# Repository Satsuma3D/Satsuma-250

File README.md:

# Satsuma 250

This project is incomplete. I might pick it up one day, or you are welcome to yourselves.

GPLv3 Licensed.

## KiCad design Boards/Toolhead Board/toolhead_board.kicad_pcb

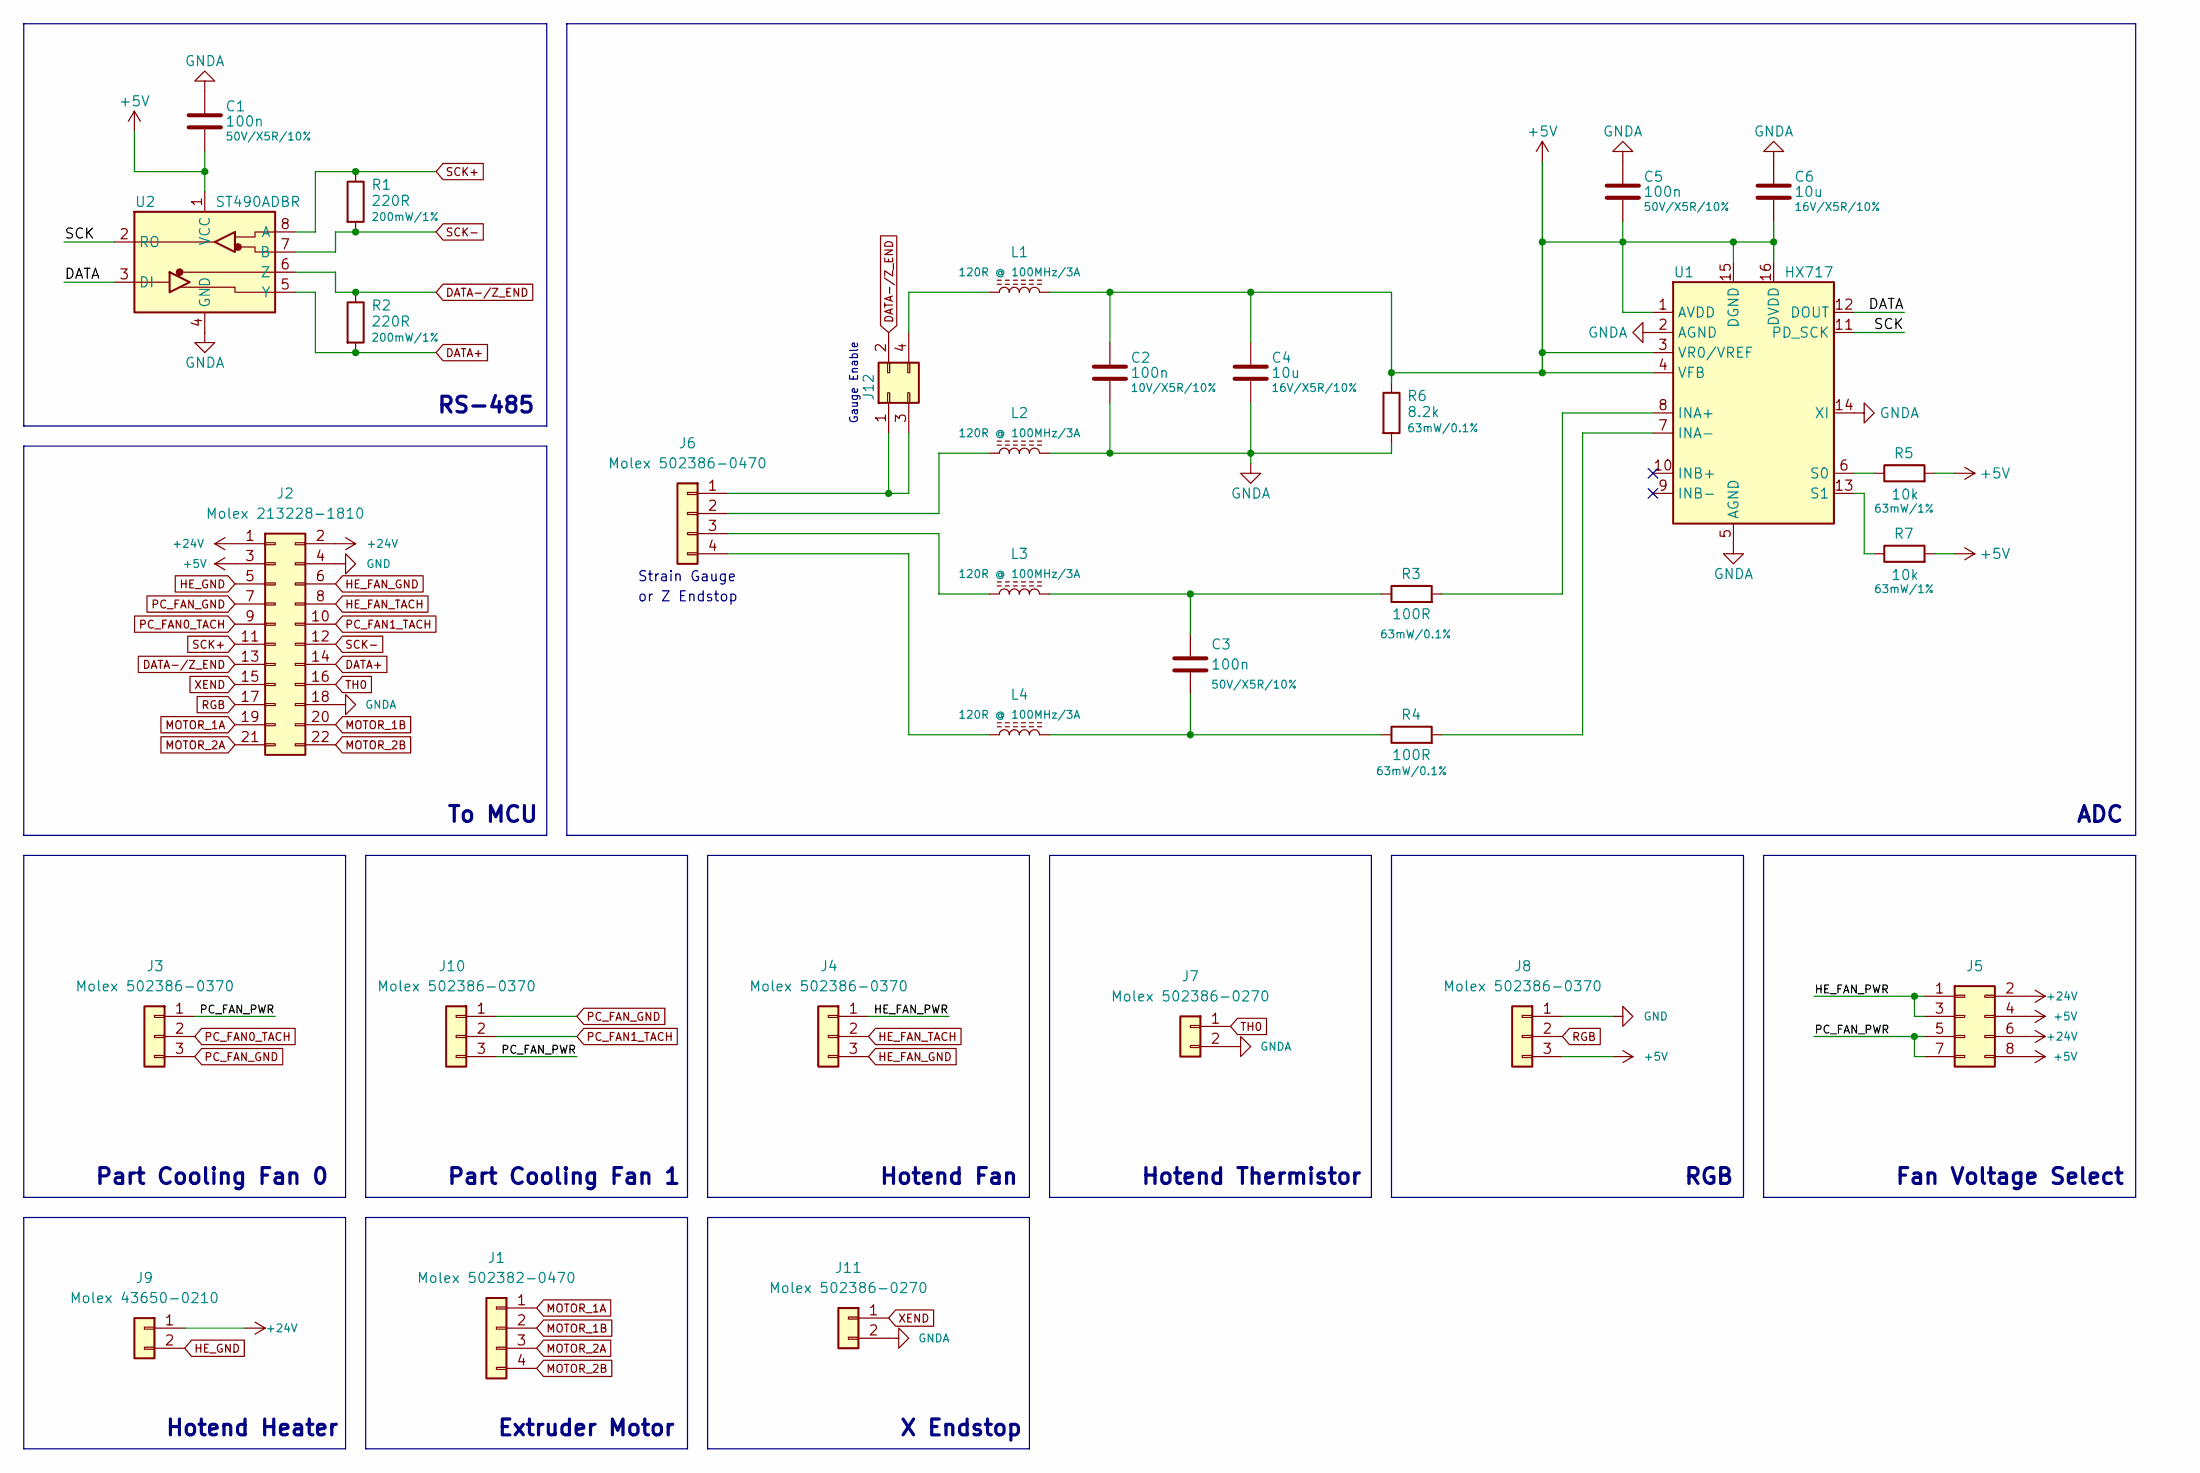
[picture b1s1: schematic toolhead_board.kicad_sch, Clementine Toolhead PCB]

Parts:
C1: 100n; C_0603_1608Metric
C2, C3, C5: 100n; C_0201_0603Metric
C4, C6: 10u; C_1206_3216Metric
J1: Molex 502382-0470; Molex_CLIK-Mate_502382-0470_1x04-1MP_P1.25mm_Vertical
J2: Molex 213228-1810; Molex_CLIK-Mate_213228-2210_1MP_P1.50mm_Horizontal
J3, J4, J8, J10: Molex 502386-0370; Molex_CLIK-Mate_502386-0370_1x03-1MP_P1.25mm_Horizontal
J5: Conn_02x04_Odd_Even; PinHeader_2x04_P2.00mm_Vertical
J6: Molex 502386-0470; Molex_CLIK-Mate_502386-0470_1x04-1MP_P1.25mm_Horizontal
J7, J11: Molex 502386-0270; Molex_CLIK-Mate_502386-0270_1x02-1MP_P1.25mm_Horizontal
J9: Molex 43650-0210; Molex_Micro-Fit_3.0_43650-0210_1x02-1MP_P3.00mm_Horizontal
J12: Conn_02x02_Odd_Even; PinHeader_2x02_P2.00mm_Vertical
L1, L2, L3, L4: 120R @ 100MHz/3A; R_0805_2012Metric
R1, R2: 220R; R_0603_1608Metric
R3, R4: 100R; R_1206_3216Metric
R5, R7: 10k; R_1206_3216Metric
R6: 8.2k; R_0201_0603Metric
U1: HX717; SOIC-16_3.9x9.9mm_P1.27mm
U2: ST490ADBR; SO-8_3.9x4.9mm_P1.27mm

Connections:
+5V: C1.2, C2.1, C4.1, C5.2, C6.2, J2.3, J5.4, J5.8, J8.3, L1.2, R5.2, R6.1, R7.2, U1.1 (AVDD), U1.3 (VR0/VREF), U1.4 (VFB), U1.15 (DGND), U1.16 (DVDD), U2.1 (VCC)
+24V: J2.1, J2.2, J5.2, J5.6, J9.1
/DATA: U1.12 (DOUT), U2.3 (DI)
/HE_FAN_PWR: J4.1, J5.1, J5.3
/PC_FAN_PWR: J3.1, J5.5, J5.7, J10.3
/SCK: U1.11 (PD_SCK), U2.2 (RO)
DATA+: J2.14, R2.2, U2.5 (Y)
DATA-/Z_END: J2.13, J12.2, R2.1, U2.6 (Z)
GND: J2.4, J8.1
GNDA: C1.1, C2.2, C4.2, C5.1, C6.1, J2.18, J7.2, J11.2, L2.2, R6.2, U1.2 (AGND), U1.5 (AGND), U1.14 (XI), U2.4 (GND)
HE_FAN_GND: J2.6, J4.3
HE_FAN_TACH: J2.8, J4.2
HE_GND: J2.5, J9.2
MOTOR_1A: J1.1, J2.19
MOTOR_1B: J1.2, J2.20
MOTOR_2A: J1.3, J2.21
MOTOR_2B: J1.4, J2.22
unnamed: C3.1, L3.2, R3.1
unnamed: C3.2, L4.2, R4.1
unnamed: J6.2, L2.1
unnamed: J6.3, L3.1
unnamed: J6.4, L4.1
unnamed: J6.1, J12.1, J12.3
unnamed: J12.4, L1.1
unnamed: R3.2, U1.8 (INA+)
unnamed: R4.2, U1.7 (INA-)
unnamed: R5.1, U1.6 (S0)
unnamed: R7.1, U1.13 (S1)
PC_FAN0_TACH: J2.9, J3.2
PC_FAN1_TACH: J2.10, J10.2
PC_FAN_GND: J2.7, J3.3, J10.1
RGB: J2.17, J8.2
SCK+: J2.11, R1.1, U2.8 (A)
SCK-: J2.12, R1.2, U2.7 (B)
TH0: J2.16, J7.1
XEND: J2.15, J11.1

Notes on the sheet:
Strain Gauge
Part Cooling Fan 0
X Endstop
Hotend Thermistor
or Z Endstop
Hotend Heater
Fan Voltage Select
RS-485
Hotend Fan
To MCU
Gauge Enable
RGB
Extruder Motor
ADC
Part Cooling Fan 1

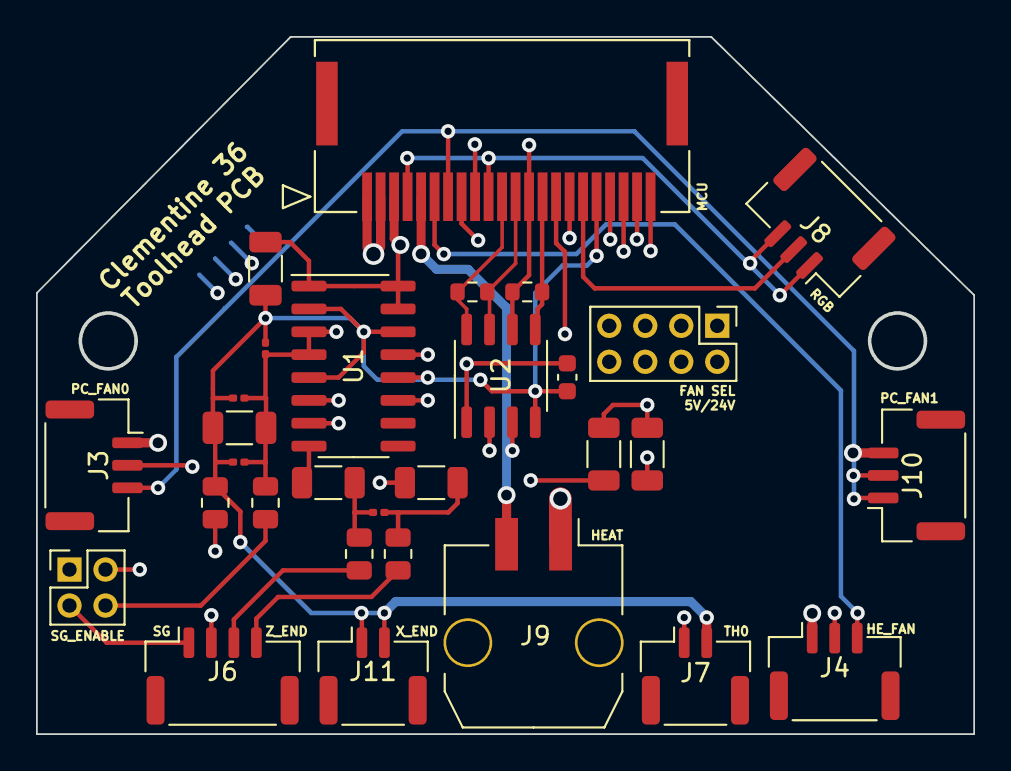
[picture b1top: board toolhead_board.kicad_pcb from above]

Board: 4 copper layers, 52.0 x 38.6 mm, 31 parts (1 on the bottom side), 36 nets.

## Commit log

2024-03-17 Update CAD
2024-03-18 Single Y extrusions
2024-03-29 CT36 Toolhead PCB
2024-03-29 Add README.md to CT36
2024-03-29 4 layer board
2024-03-29 Update image
2024-03-29 Belt paths
2024-03-30 New A/B motor assemblies
2024-03-30 Bridge cutting A/B mounts, Git LFS
2024-03-30 Add blind joints to frame
2024-03-30 Front frame blind joints are different; add gantry fasteners
2024-03-30 Fix side panel sizing
2024-03-30 Y endstop pod
2024-03-30 Cleanup the look of that ugly door
2024-03-30 Nicer side panels
2024-03-31 XY Joints
2024-04-01 Front idlers - cheers, Clee
2024-04-01 Updated render
2024-04-01 Electronics re-jig, cleaner XY joint tops
2024-04-01 Use filtered mains inlets
2024-04-01 Begun filtered mains IEC
2024-04-03 Frame updates
2024-04-03 Remove Git LFS
2024-04-23 Satsuma 250 from here on
2024-04-23 Toolhead layout
2024-05-07 Bed mounting refinements
2024-05-08 Top Z mount
2024-05-11 Z rod joints complete
2024-05-12 Gantry update
2024-05-15 A Belt
2024-05-16 Begin manual
2024-05-17 Refined motor mounts and top rod mounts
2024-05-17 Trident Z leadscrew support
2024-05-20 Pre-manual
2024-05-20 Add warning triangle
2024-05-20 Begin frame
2024-05-22 Frame preparation
2024-05-22 Grammar fix
2024-05-22 Blind joint preparation
2024-05-23 Faster process entirely in Fusion
2024-05-23 First blind joint
2024-05-28 New gantry
2024-05-28 Update screws
2024-05-28 Cleanup screws
2024-05-29 5mm rods
2024-06-15 Z motor mounts for quad motors
2024-06-15 Polish Z motor mounts, foot corners
2024-06-15 Fix mirrored text on motor B mounts
2024-06-16 Fix corner chamfer printability
2024-06-16 Improved cross bridge and horizontal holes
2024-07-21 Parametric assembly
2024-07-21 Bed extrusions
2024-07-21 Fix top plate rod alignment
2024-07-21 Finalizing the bed
2024-07-22 Fix bed mounting, add bearing cutouts
2024-07-22 Fix bed bracket B chamfer
2024-07-22 Leadscrew nut blocks
2024-07-22 Re export rod plates
2024-07-22 Fix MakerbeamXL slot width
2024-07-22 Update render
2024-08-17 Side panels and stuff
2024-08-17 Material fixes
2024-08-17 Engine example
2024-08-18 New backpack
2024-08-18 PTFE tube entry
2024-08-18 Update LCD
2024-08-18 LCD mounts
2024-08-21 Updating bed bearing holders
2024-08-21 New bed mounts
2024-11-11 Add rubber feet final parts
2024-11-13 Add bed corners
2024-11-20 Updating designs
2024-11-23 Export final Z rod parts; motor plates
2024-11-23 Bed bearing corners
2025-04-15 Upload incomplete CAD
2025-04-15 Remove old
